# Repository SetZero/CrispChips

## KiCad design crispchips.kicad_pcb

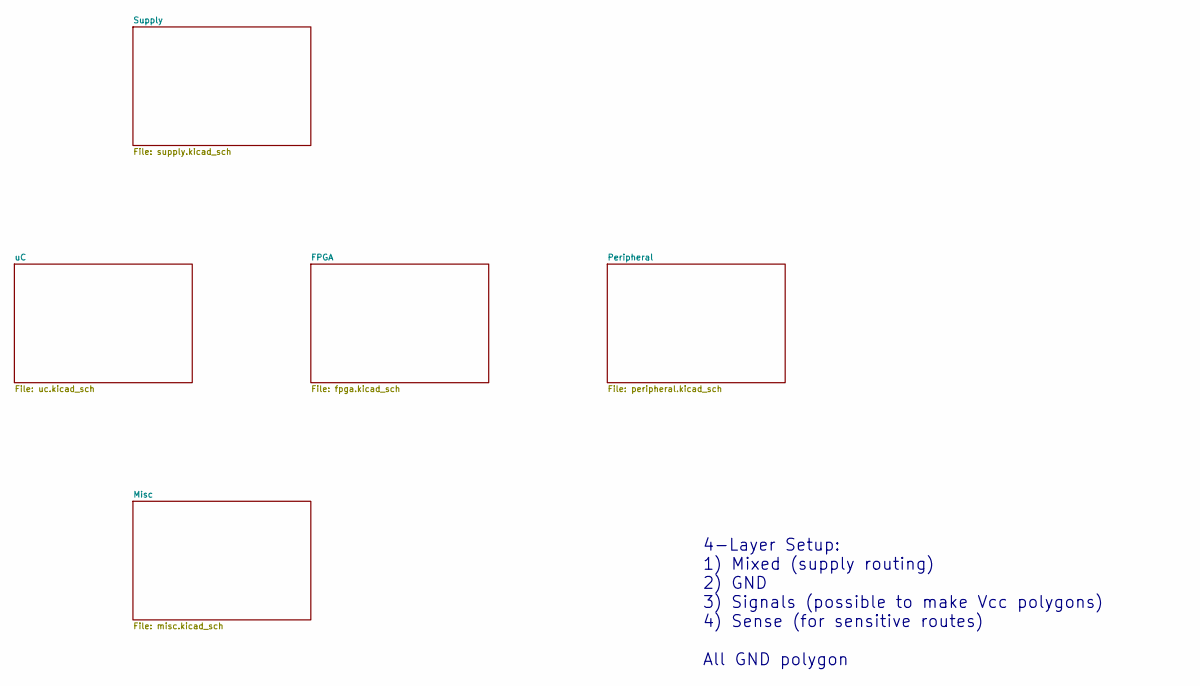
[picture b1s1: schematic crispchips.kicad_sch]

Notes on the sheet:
4-Layer Setup: 1) Mixed (supply routing) 2) GND 3) Signals (possible to make Vcc polygons) 4) Sense (for sensitive routes) All GND polygon

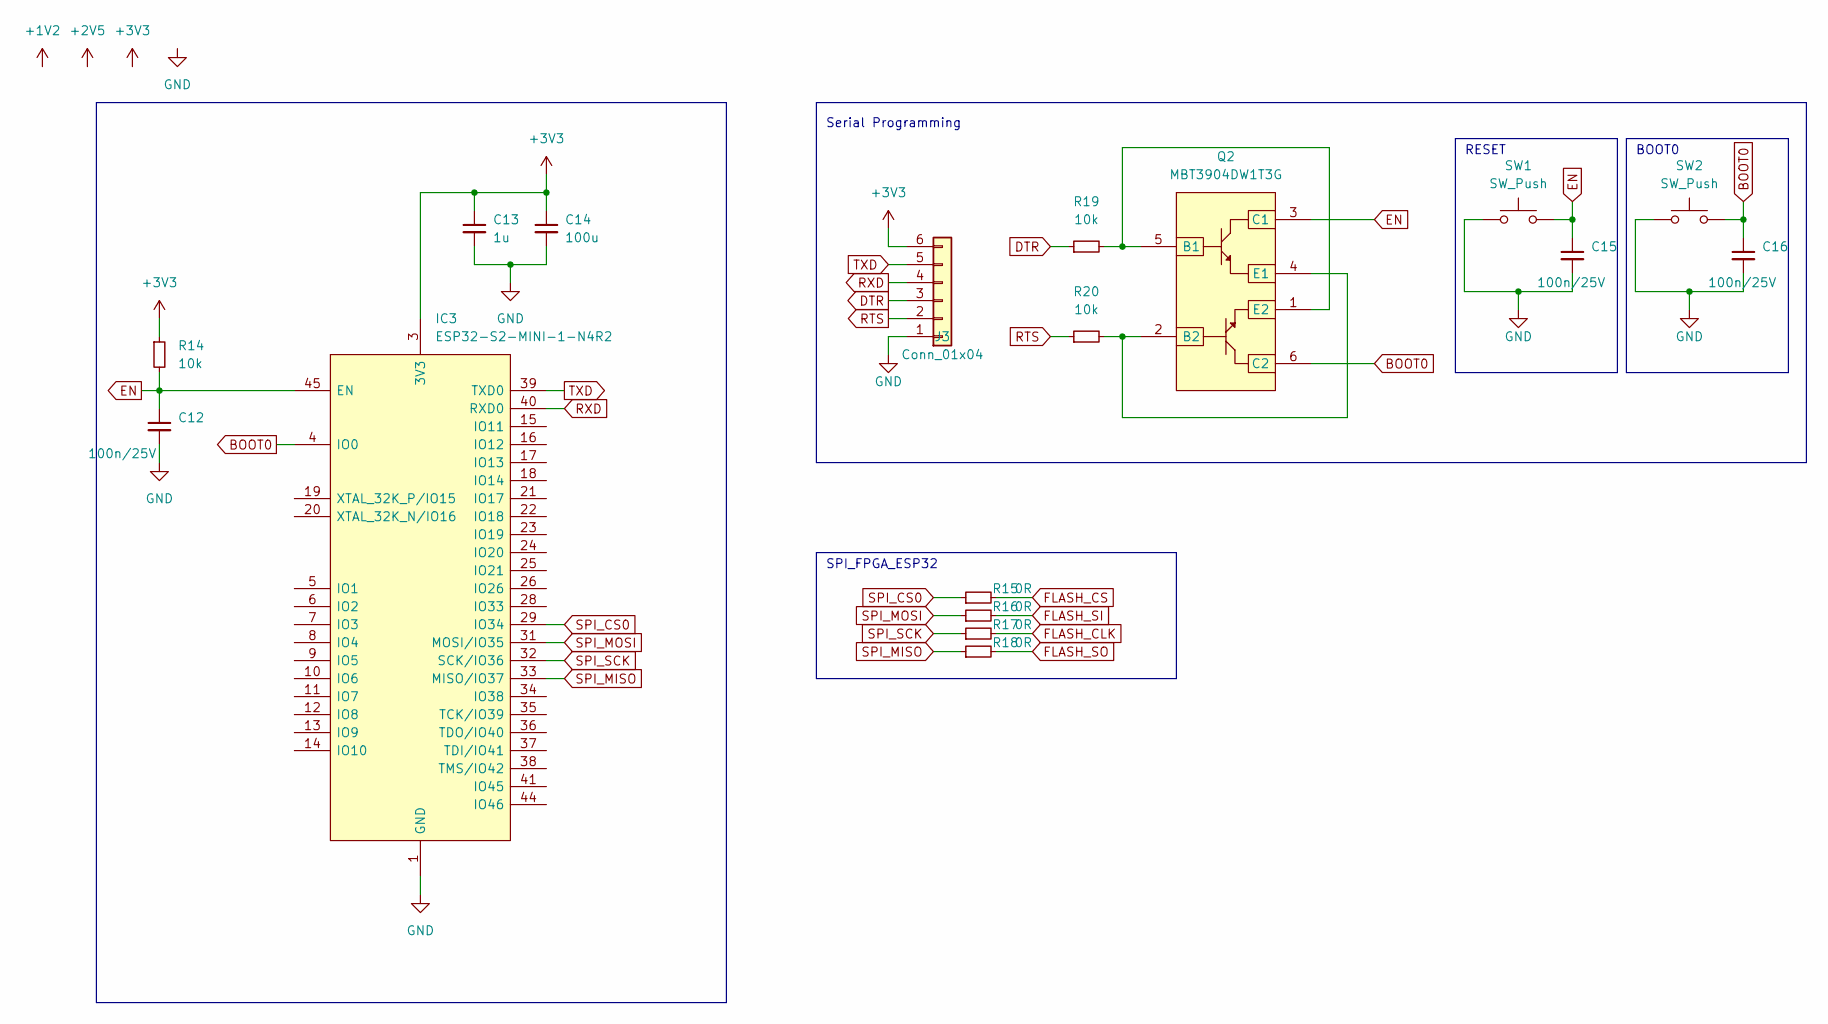
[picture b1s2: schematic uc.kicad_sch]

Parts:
C12, C15, C16: 100n/25V; C_0603_1608Metric_Pad1.08x0.95mm_HandSolder
C13: 1u; C_0603_1608Metric_Pad1.08x0.95mm_HandSolder
C14: 100u; C_0603_1608Metric_Pad1.08x0.95mm_HandSolder
IC3: ESP32-S2-MINI-1-N4R2; ESP32S2MINI1N4R2; Mouser Part Number 356-ESP32S2MINI1N4R2
J3: Conn_01x04; PinHeader_1x04_P2.54mm_Vertical
Q2: MBT3904DW1T3G; SOT65P210X110-6N; Mouser Part Number 863-MBT3904DW1T3G
R14, R19, R20: 10k; R_0603_1608Metric_Pad0.98x0.95mm_HandSolder
R15, R16, R17, R18: 0R; R_0603_1608Metric_Pad0.98x0.95mm_HandSolder
SW1, SW2: SW_Push

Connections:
BOOT0: C16.1, IC3.4 (IO0), Q2.6 (C2), SW2.2
DTR: J3.3, R19.1
EN: C12.1, C15.1, IC3.45 (EN), Q2.3 (C1), R14.2, SW1.2
FLASH_CLK: R17.2; also elsewhere on the board
FLASH_CS: R15.2; also elsewhere on the board
FLASH_SI: R16.2; also elsewhere on the board
FLASH_SO: R18.2; also elsewhere on the board
GND: C12.2, C13.2, C14.2, C15.2, C16.2, IC3.1 (GND), IC3.2 (GND_2), IC3.30 (GND_3), IC3.42 (GND_4), IC3.43 (GND_5), IC3.46 (GND_6), IC3.47 (GND_7), IC3.48 (GND_8), IC3.49 (GND_9), IC3.50 (GND_10), IC3.51 (GND_11), IC3.52 (GND_12), IC3.53 (GND_13), IC3.54 (GND_14), IC3.55 (GND_15), IC3.56 (GND_16), IC3.57 (GND_17), IC3.58 (GND_18), IC3.59 (GND_19), IC3.60 (GND_20), IC3.61 (GND_21), IC3.62 (GND_22), IC3.63 (GND_23), IC3.64 (GND_24), IC3.65 (GND_25), IC3.66 (GND_26), IC3.67 (GND_27), IC3.68 (GND_28), IC3.69 (GND_29), IC3.70 (GND_30), IC3.71 (GND_31), IC3.72 (GND_32), IC3.73 (GND_33), J3.1, SW1.1, SW2.1; also elsewhere on the board
ISL_3V3: C13.1, C14.1, IC3.3 (3V3), J3.6, R14.1; also elsewhere on the board
unnamed: Q2.1 (E2), Q2.5 (B1), R19.2
unnamed: Q2.2 (B2), Q2.4 (E1), R20.2
RTS: J3.2, R20.1
RXD: IC3.40 (RXD0), J3.4
SPI_CS0: IC3.29 (IO34), R15.1; also elsewhere on the board
SPI_MISO: IC3.33 (MISO/IO37), R18.1; also elsewhere on the board
SPI_MOSI: IC3.31 (MOSI/IO35), R16.1; also elsewhere on the board
SPI_SCK: IC3.32 (SCK/IO36), R17.1; also elsewhere on the board
TXD: IC3.39 (TXD0), J3.5

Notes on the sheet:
BOOT0
Serial Programming
SPI_FPGA_ESP32
RESET

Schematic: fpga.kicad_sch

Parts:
C17, C18, C19, C20, C21, C22, C23, C24, C25, C26, C27, C28, C29, C30, C31, C32, C33, C34, C35, C36, C37, C38, C39: 100n/25V; C_0603_1608Metric_Pad1.08x0.95mm_HandSolder
D1: DIODE; SODFL1608X70N
D2: DIODE; DIOM5126X265N
D3, D9: RCLAMP0524PATCT; Mouser Part Number 947-RCLAMP0524PATCT
D4, D5, D6, D7, D8: D_TVS; R_0603_1608Metric_Pad0.98x0.95mm_HandSolder
F1: 1812L160_12DR; 1812L010DR; Mouser Part Number 576-1812L160/12DR
IC4: XC3S250E-4VQG100C; QFP50P1600X1600X120-100N; Mouser Part Number 217-C3S250E-4VQG100C
IC5: PCA9306DCUR; SOP50P310X90-8N; Mouser Part Number 595-PCA9306DCUR
IC6: W25N512GVEIG; SON127P800X600X80-9N-D; Mouser Part Number 454-W25N512GVEIG
J4: JTAG; PinHeader_1x06_P2.54mm_Vertical
J5: HDMI_A; HD0419THTR
Q3: FDV301N; SOT96P237X111-3N; Mouser Part Number 512-FDV301N
R21, R23, R28, R29, R30, R42: 0R; R_0603_1608Metric_Pad0.98x0.95mm_HandSolder
R22: 100k; R_0603_1608Metric_Pad0.98x0.95mm_HandSolder
R24: 10k; R_0603_1608Metric_Pad0.98x0.95mm_HandSolder
R25, R26, R31, R32: 4k7; R_0603_1608Metric_Pad0.98x0.95mm_HandSolder
R27: 200k; R_0603_1608Metric_Pad0.98x0.95mm_HandSolder
R33, R34, R35, R36, R37, R38, R39, R41: 49R9; R_0603_1608Metric_Pad0.98x0.95mm_HandSolder
R40: DNP; R_0603_1608Metric_Pad0.98x0.95mm_HandSolder
X1: ECS-2016MV-500-BN-TR3; Oscillator_DIP-14

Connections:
FLASH_CLK: IC6.6 (CLK); also elsewhere on the board
FLASH_CS: IC4.24 (IO_L01P_2/CSO_B), IC6.1 (~CS), R40.1; also elsewhere on the board
FLASH_SCK: IC4.50 (IO_L09N_2/CCLK)
FLASH_SI: IC4.27 (IO_L02N_2/MOSI/CSI_B), IC6.5 (DI_(IO0)); also elsewhere on the board
FLASH_SO: IC4.44 (IO_L07N_2/DIN/D0), IC6.2 (DO_(IO1)); also elsewhere on the board
FPGA_HDMI_SCL: IC5.3 (SCL1), R31.1
FPGA_HDMI_SDA: IC5.4 (SDA1), R32.1
FPGA_TCK: IC4.77 (TCK), J4.3
FPGA_TDI: IC4.100 (TDI), J4.5
FPGA_TDO: IC4.76 (TDO), J4.4
FPGA_TMS: IC4.75 (TMS), J4.6
GND: C17.2, C18.2, C19.2, C20.2, C21.2, C22.2, C23.2, C24.2, C25.2, C26.2, C27.2, C28.2, C29.2, C38.2, C39.2, D3.3 (GND_1), D3.8 (GND_2), D4.1 (A1), D5.1 (A1), D6.1 (A1), D7.1 (A1), D8.1 (A1), D9.3 (GND_1), D9.8 (GND_2), IC4.7 (GND_1), IC4.14 (GND_2), IC4.19 (GND_3), IC4.29 (GND_4), IC4.37 (GND_5), IC4.52 (GND_6), IC4.59 (GND_7), IC4.64 (GND_8), IC4.72 (GND_9), IC4.81 (GND_10), IC4.87 (GND_11), IC4.93 (GND_12), IC5.1 (GND), IC6.4 (GND), IC6.9 (EP), J4.2, J5.17 (GND), R42.2, X1.7 (GND); also elsewhere on the board
HDMI_5V: C28.1, C39.1, D2.2 (K), D4.2 (A2), J5.18 (+5V), R25.2, R26.2, R27.2
HDMI_CEC: D8.2 (A2), IC4.78 (IO_L01P_0), J5.13 (CEC), R23.1
HDMI_CLK_M: C37.1, C37.2, D9.5 (INPUT_LINES_4), D9.6 (OUTUT_LINES_(NIC)_1), IC4.91 (IO_L05N_0/GCLK11), J5.12 (CK-), R41.1
HDMI_CLK_P: C36.1, C36.2, D9.4 (INPUT_LINES_3), D9.7 (OUTUT_LINES_(NIC)_2), IC4.90 (IO_L05P_0/GCLK10), J5.10 (CK+), R39.1
HDMI_D0_M: C35.1, C35.2, D9.2 (INPUT_LINES_2), D9.9 (OUTUT_LINES_(NIC)_3), IC4.12 (IO_L04N_3/LHCLK3), J5.9 (D0-), R38.1
HDMI_D0_P: C34.1, C34.2, D9.1 (INPUT_LINES_1), D9.10 (OUTUT_LINES_(NIC)_4), IC4.11 (IO_L04P_3/LHCLK2), J5.7 (D0+), R37.1
HDMI_D1_M: C33.1, C33.2, D3.5 (INPUT_LINES_4), D3.6 (OUTUT_LINES_(NIC)_1), IC4.10 (IO_L03N_3/LHCLK1), J5.6 (D1-), R36.1
HDMI_D1_P: C32.1, C32.2, D3.4 (INPUT_LINES_3), D3.7 (OUTUT_LINES_(NIC)_2), IC4.9 (IO_L03P_3/LHCLK0), J5.4 (D1+), R35.1
HDMI_D2_M: C31.1, C31.2, D3.2 (INPUT_LINES_2), D3.9 (OUTUT_LINES_(NIC)_3), IC4.2 (IO_L01P_3), J5.3 (D2-), R34.1
HDMI_D2_P: C30.1, C30.2, D3.1 (INPUT_LINES_1), D3.10 (OUTUT_LINES_(NIC)_4), IC4.3 (IO_L01N_3), J5.1 (D2+), R33.1
HDMI_HPD: D5.2 (A2), J5.19 (HPD), Q3.1, R22.1
HDMI_SCL: D7.2 (A2), IC4.85 (IO_L03P_0/GCLK6), IC5.6 (SCL2), J5.15 (SCL), R25.1
HDMI_SDA: D6.2 (A2), IC4.53 (IO_L01P_1), IC5.5 (SDA2), J5.16 (SDA), R26.1
HDMI_TX_HPD: IC4.54 (IO_L01N_1), Q3.3, R24.2
ISL_1V2: C18.1, C21.1, C24.1, C27.1, IC4.6 (VCCINT_1), IC4.28 (VCCINT_2), IC4.56 (VCCINT_3), IC4.80 (VCCINT_4); also elsewhere on the board
ISL_2V5_LDO: C17.1, C20.1, C23.1, C26.1, IC4.21 (VCCAUX_1), IC4.46 (VCCAUX_2), IC4.74 (VCCAUX_3), IC4.96 (VCCAUX_4), J4.1, R21.1; also elsewhere on the board
ISL_3V3: C19.1, C22.1, C25.1, C29.1, C38.1, D1.1 (A), IC4.8 (VCCO_3_1), IC4.20 (VCCO_3_2), IC4.31 (VCCO_2_1), IC4.45 (VCCO_2_2), IC4.55 (VCCO_1_1), IC4.73 (VCCO_1_2), IC4.82 (VCCO_0_1), IC4.97 (VCCO_0_2), IC5.2 (VREF1), IC6.8 (VCC), R24.1, R28.1, R29.1, R30.1, R31.2, R32.2, R33.2, R34.2, R35.2, R36.2, R37.2, R38.2, R39.2, R40.2, R41.2, X1.14 (Vcc); also elsewhere on the board
ISL_5V: F1.2; also elsewhere on the board
unnamed: D1.2 (K), R23.2
unnamed: D2.1 (A), F1.1
unnamed: IC4.1 (PROG_B), R21.2
unnamed: IC5.7 (VREF2), IC5.8 (EN), R27.1
unnamed: IC6.3 (~WP_(IO2)), R29.2
unnamed: IC6.7 (~HOLD_(IO3)), R30.2
unnamed: J5.2 (D2S), J5.5 (D1S), J5.8 (D0S), J5.11 (CKS), J5.SH, R42.1
unnamed: Q3.2, R22.2
unnamed: R28.2, X1.1 (Tri-State)
OSC_IN: IC4.89 (IP_L04N_0/GCLK9), X1.8 (OUT)
SPI_CS0: IC4.57 (IO_L02P_1); also elsewhere on the board
SPI_MISO: IC4.79 (IO_L01N_0); also elsewhere on the board
SPI_MOSI: IC4.58 (IO_L02N_1); also elsewhere on the board
SPI_SCK: IC4.86 (IO_L03N_0/GCLK7); also elsewhere on the board

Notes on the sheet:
VCCINT
VCCO
HDMI HPD
HDMI Connector + ESD
USBekistan
I2C
JTAG
QSPI FLASH
HDMI CEC
HDMI 5V Protection
TVS
CLK
VCCAUX

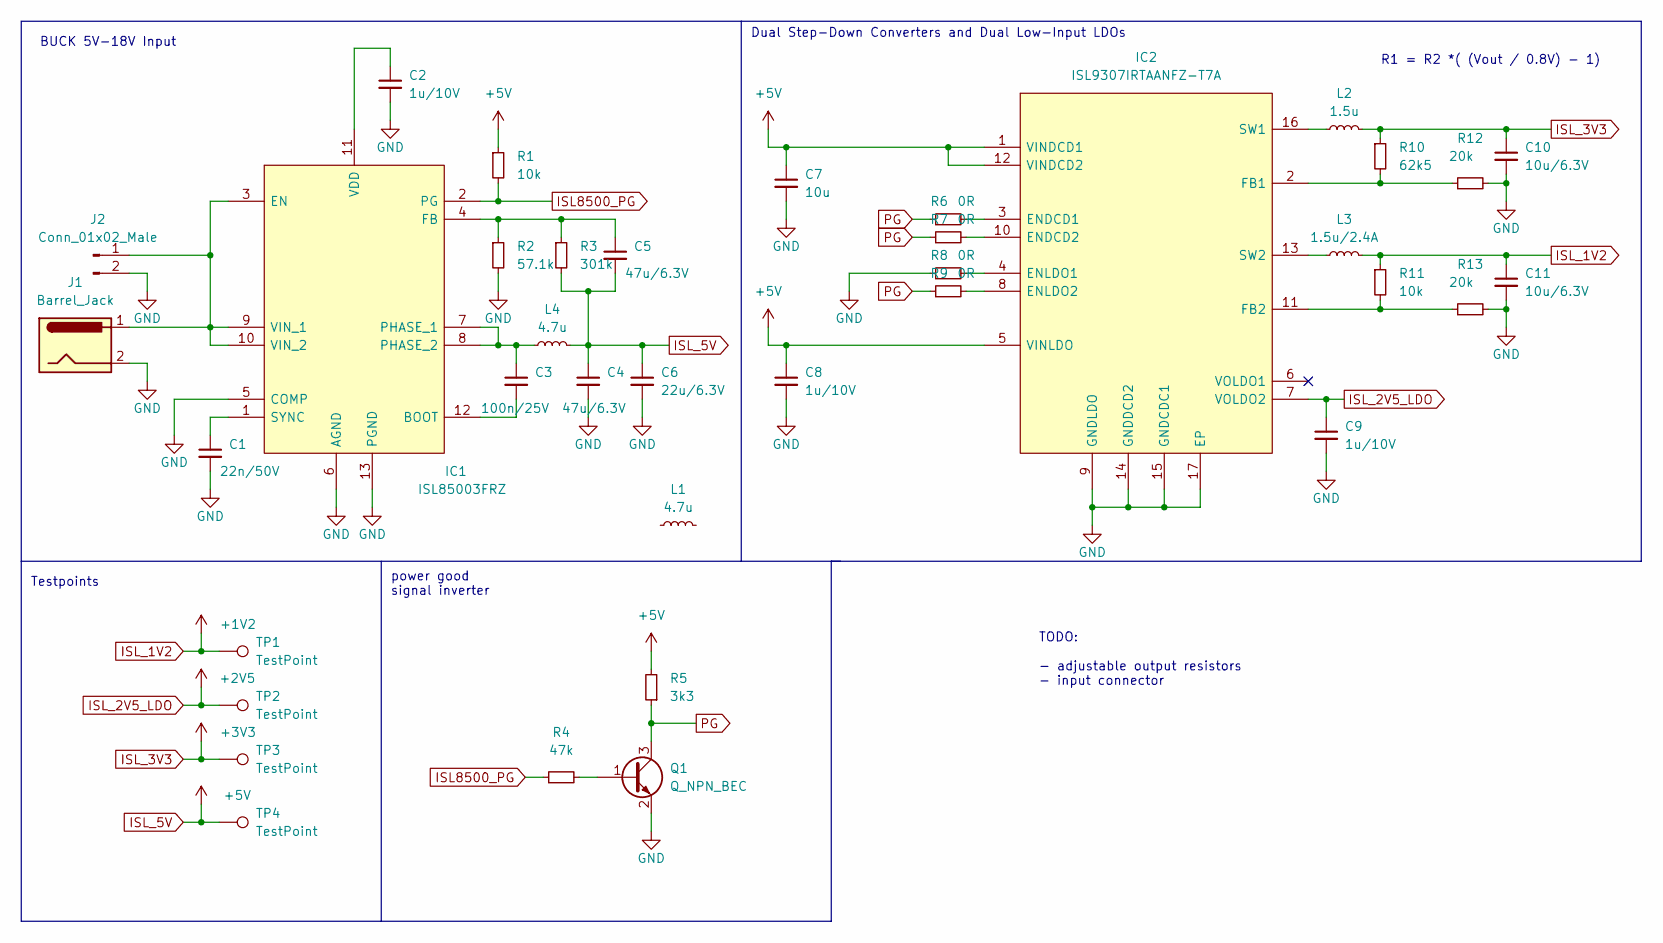
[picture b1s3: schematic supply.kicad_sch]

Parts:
C1: 22n/50V; C_0603_1608Metric_Pad1.08x0.95mm_HandSolder
C2, C8, C9: 1u/10V; C_0603_1608Metric_Pad1.08x0.95mm_HandSolder
C3: 100n/25V; C_0603_1608Metric_Pad1.08x0.95mm_HandSolder
C4, C5: 47u/6.3V; C_0603_1608Metric_Pad1.08x0.95mm_HandSolder
C6: 22u/6.3V; C_0603_1608Metric_Pad1.08x0.95mm_HandSolder
C7: 10u; C_0603_1608Metric_Pad1.08x0.95mm_HandSolder
C10, C11: 10u/6.3V; C_0603_1608Metric_Pad1.08x0.95mm_HandSolder
IC1: ISL85003FRZ; SON50P300X400X90-13N; Mouser Part Number 968-ISL85003FRZ
IC2: ISL9307IRTAANFZ-T7A; QFN65P400X400X75-17N; Mouser Part Number 968-IS9307IRTAANFZT7
J1: Barrel_Jack; PJ063BH
J2: Conn_01x02_Male; PinHeader_1x02_P2.54mm_Vertical
L1: 4.7u; NR5040T4R7N
L2: 1.5u; L_1008_2520Metric_Pad1.43x2.20mm_HandSolder
L3: 1.5u/2.4A; L_1008_2520Metric_Pad1.43x2.20mm_HandSolder
L4: 4.7u; L_Taiyo-Yuden_NR-50xx
Q1: Q_NPN_BEC; TO-236AB
R1, R11: 10k; R_0603_1608Metric_Pad0.98x0.95mm_HandSolder
R2: 57.1k; R_0603_1608Metric_Pad0.98x0.95mm_HandSolder
R3: 301k; R_0603_1608Metric_Pad0.98x0.95mm_HandSolder
R4: 47k; R_0603_1608Metric_Pad0.98x0.95mm_HandSolder
R5: 3k3; R_0603_1608Metric_Pad0.98x0.95mm_HandSolder
R6, R7, R8, R9: 0R; R_0603_1608Metric_Pad0.98x0.95mm_HandSolder
R10: 62k5; R_0603_1608Metric_Pad0.98x0.95mm_HandSolder
R12, R13: 20k; R_0603_1608Metric_Pad0.98x0.95mm_HandSolder
TP1, TP2, TP3, TP4: TestPoint; TestPoint_THTPad_D1.5mm_Drill0.7mm

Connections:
GND: C1.2, C2.2, C4.2, C6.2, C7.2, C8.2, C9.2, C10.2, C11.2, IC1.5 (COMP), IC1.6 (AGND), IC1.13 (PGND), IC2.9 (GNDLDO), IC2.14 (GNDDCD2), IC2.15 (GNDCDC1), IC2.17 (EP), J1.2, J2.2, Q1.2 (E), R2.2, R8.1, R12.2, R13.2; also elsewhere on the board
ISL8500_PG: IC1.2 (PG), R1.2, R4.1
ISL_1V2: C11.1, L3.2, R11.1, TP1.1; also elsewhere on the board
ISL_2V5_LDO: C9.1, IC2.7 (VOLDO2), TP2.1; also elsewhere on the board
ISL_3V3: C10.1, L2.2, R10.1, TP3.1; also elsewhere on the board
ISL_5V: C4.1, C5.2, C6.1, C7.1, C8.1, IC2.1 (VINDCD1), IC2.5 (VINLDO), IC2.12 (VINDCD2), L4.2, R1.1, R3.2, R5.2, TP4.1; also elsewhere on the board
unnamed: C1.1, IC1.1 (SYNC)
unnamed: C2.1, IC1.11 (VDD)
unnamed: C3.1, IC1.7 (PHASE_1), IC1.8 (PHASE_2), L4.1
unnamed: C3.2, IC1.12 (BOOT)
unnamed: C5.1, IC1.4 (FB), R2.1, R3.1
unnamed: IC1.3 (EN), IC1.9 (VIN_1), IC1.10 (VIN_2), J1.1, J2.1
unnamed: IC2.2 (FB1), R10.2, R12.1
unnamed: IC2.3 (ENDCD1), R6.2
unnamed: IC2.4 (ENLDO1), R8.2
unnamed: IC2.8 (ENLDO2), R9.2
unnamed: IC2.10 (ENDCD2), R7.2
unnamed: IC2.11 (FB2), R11.2, R13.1
unnamed: IC2.13 (SW2), L3.1
unnamed: IC2.16 (SW1), L2.1
unnamed: Q1.1 (B), R4.2
PG: Q1.3 (C), R5.1, R6.1, R7.1, R9.1

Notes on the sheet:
BUCK 5V-18V Input
power good signal inverter
R1 = R2 *( (Vout / 0.8V) - 1)
TODO: - adjustable output resistors - input connector
Dual Step-Down Converters and Dual Low-Input LDOs
Testpoints

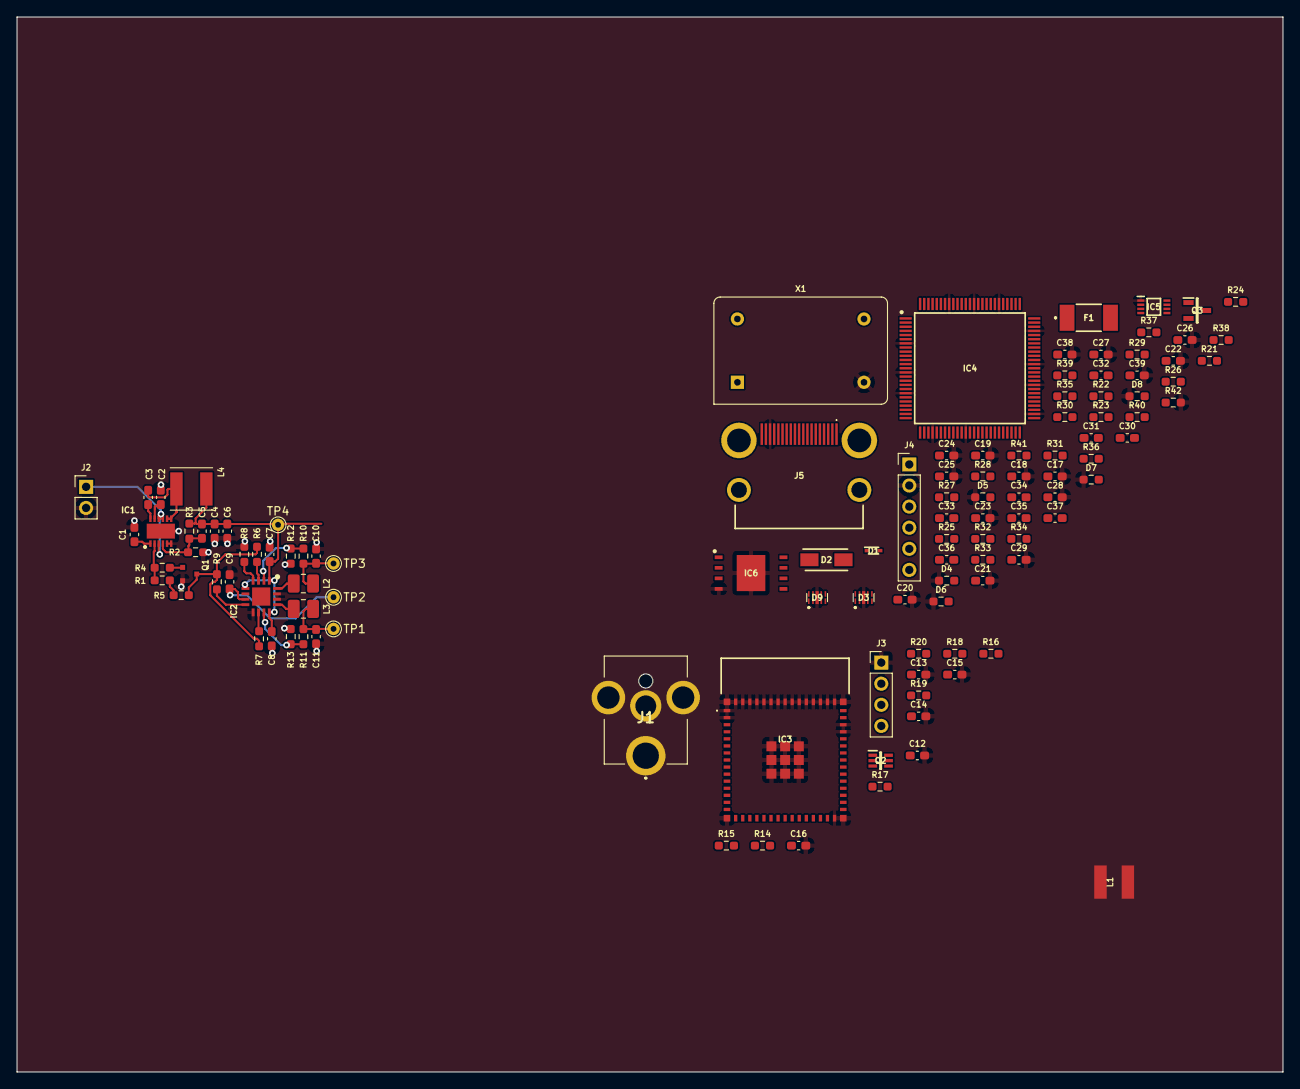
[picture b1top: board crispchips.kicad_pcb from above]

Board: 2 copper layers, 152.4 x 127.0 mm, 114 parts (0 on the bottom side), 67 nets.

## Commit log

2022-04-09 setup kicad project
2022-04-09 deleted old file
2022-04-10 added first symbols/footprints
2022-04-10 add fpga, power and flash to schematics
2022-04-11 added ESP32-S2-Mini libraries
2022-04-11 Added global VCC and GND lables
2022-04-11 updated ESP32S2MINI1N4R2.kicad_mod footprint
2022-04-11 now using correct VCC and GND symbols
2022-04-11 added esp32 schematic && updated supply symbols
2022-04-11 added todo in uC
2022-04-11 updated TODO
2022-04-13 Added Supply
2022-04-13 modified supply symbols + added layout
2022-04-13 fpga powa
2022-04-14 supply: changed voltage divider values on ISL9307
2022-04-14 supply: added formula for buck voltage dividers
2022-04-15 supply: added barrel jack
2022-04-15 ignore backups
2022-04-15 added hdmi
2022-04-18 power good signal inversion && added part numbers
2022-04-18 Add fpga HDMI basic components
2022-04-18 added missing MNR && footprint to inductor added footprint to test points
2022-04-19 added ESD ic to fpga.kicad_sym
2022-04-19 added new IC to fpga.kicad_sch && changed sheet size of fpga.kicad_sch to A3
2022-04-21 Added HDMI to FPGA
2022-04-23 removed JTAG, added bootstrap circuit
2022-04-23 added auto program table to uc.kicad_sch
2022-04-23 added i2c level shifter ic
2022-04-24 Added i2C level shifter + QSPI Flash to FPGA
2022-04-24 Added HDMI connections to fpga
2022-04-24 spi ESP32 implementation in uC.kicad_sch
2022-04-24 Added I2C to fpga
2022-04-24 Added SPI to FPGA
2022-04-25 fixed layout in fpga.kicad_sch
2022-04-27 updated libraries
2022-04-27 update fpga layout
2022-05-01 assigned some missing footprints
2022-05-01 added some missing footprints
2022-05-01 moved hdmi schematic
2022-05-02 update footprints for fpga
2022-05-02 Added FPGA footprints
2022-05-03 first layout steps
2022-05-03 supply layout review step
2022-05-03 supply routing
2022-05-03 added test points
2022-05-03 changed testpoint footprints
2022-05-03 supply rerouting
2022-05-03 trace cleaning
2022-05-03 added gnd planes
2022-05-03 update footprint of jack
